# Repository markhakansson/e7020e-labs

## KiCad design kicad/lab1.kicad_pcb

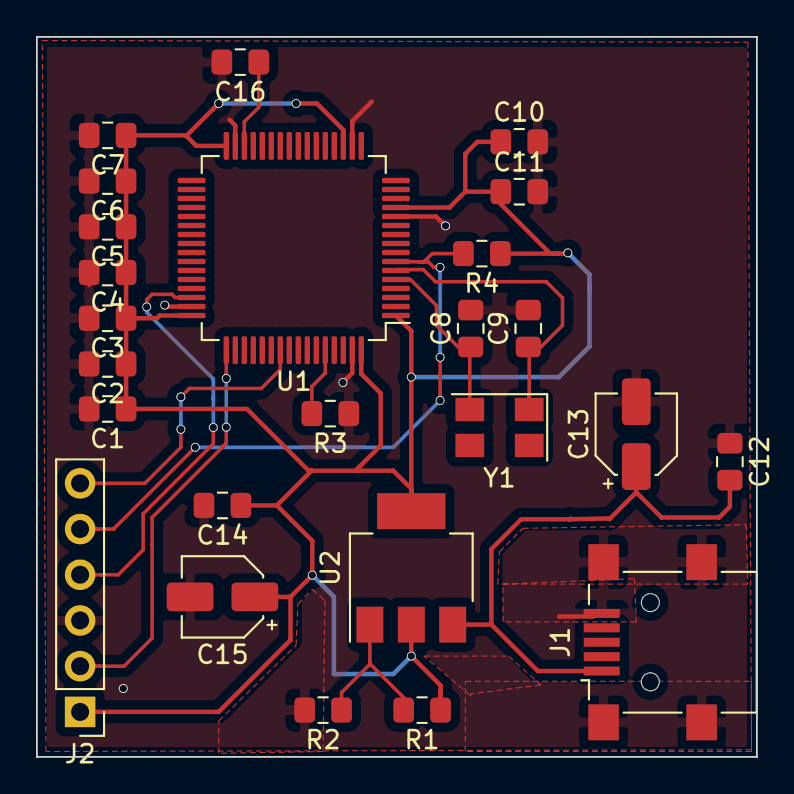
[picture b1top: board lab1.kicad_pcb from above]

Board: 2 copper layers, 40.0 x 40.0 mm, 25 parts (0 on the bottom side), 12 nets.

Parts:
C1, C2, C3, C4, C5, C6, C10, C12, C14: 100nF; C_0805_2012Metric_Pad1.15x1.40mm_HandSolder
C7, C16: 4.7uF; C_0805_2012Metric_Pad1.15x1.40mm_HandSolder
C8, C9: 18pF; C_0805_2012Metric_Pad1.15x1.40mm_HandSolder
C11: 1uF; C_0805_2012Metric_Pad1.15x1.40mm_HandSolder
C13, C15: 10uF; CP_Elec_4x4.5
J1: USB_OTG; USB_Mini-B_Lumberg_2486_01_Horizontal
J2: Conn_01x06_Male; PinHeader_1x06_P2.54mm_Vertical
R1: 2k; R_0805_2012Metric_Pad1.15x1.40mm_HandSolder
R2: 1k; R_0805_2012Metric_Pad1.15x1.40mm_HandSolder
R3, R4: 10k; R_0805_2012Metric_Pad1.15x1.40mm_HandSolder
U1: STM32F411RETx; LQFP-64_10x10mm_P0.5mm
U2: LM1117ADJ; SOT-223
Y1: 8.0Mhz; Crystal_SMD_5032-4Pin_5.0x3.2mm

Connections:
+3V3: C1.1, C2.1, C3.1, C4.1, C5.1, C6.1, C7.1, C10.1, C11.1, C14.1, C15.1, J2.1, R1.1, R4.1, U1.1, U1.13, U1.19, U1.32, U1.48, U1.64, U2.2, U2.4
+5V: C12.2, C13.1, J1.1, U2.3
/NRST: J2.5, R4.2, U1.7
/SWCLK: J2.2, U1.49
/SWDIO: J2.4, U1.46
/SWO: J2.6, U1.55
GND: C1.2, C2.2, C3.2, C4.2, C5.2, C6.2, C7.2, C8.2, C9.2, C10.2, C11.2, C12.1, C13.2, C14.2, C15.2, C16.2, J1.5, J1.6, J2.3, R2.2, R3.1, U1.12, U1.18, U1.31, U1.47, U1.63
unnamed: C8.1, U1.5, Y1.2
unnamed: C9.1, U1.6, Y1.1
unnamed: C16.1, U1.30
unnamed: R1.2, R2.1, U2.1
unnamed: R3.2, U1.60

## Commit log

2020-01-22 Lab 1 1.1 to 1.7 complete
2020-01-23 Finish 1.8-1.10
2020-01-23 Add footprint to most components
2020-01-24 Finish lab 1
2020-01-27 Finish lab 1 for real
2020-01-28 Start work on lab2
2020-01-29 Start routing copper in lab 2
2020-01-30 Finish routing, start work on adding GND plate
2020-02-03 Finish lab 2
2020-04-08 Add Rust bare labs
2020-04-08 Change name from lab1 to kicad
2020-04-08 (bare1_1) answer
2020-04-08 (bare1_2) answer
2020-04-08 (bare1_3) answer
2020-04-08 (bare1_4) answer
2020-04-10 (bare 2_1) finish bare 2
2020-04-11 (bare3_1) answers to question 1
2020-04-11 (bare3_2) add explicit types
2020-04-11 (bare3_3) answer question 3
2020-04-11 (bare3_4) push bs content into a
2020-04-11 (bare3_5) push bs content into a without loop
2020-04-11 (bare0_1) answer question 1
2020-04-11 (bare0_2) answer question 1
2020-04-11 (bare0_3) answer question 3
2020-04-11 (bare0_4) answer question 4
2020-04-11 (bare0_5) answer question 5
2020-04-12 (bare5_1) I did not enjoy the blinking
2020-04-12 (bare4_2) I did not enjoy the blinking
2020-04-12 Remove ./lab1 kicad files, as they are placed in ./kicad
2020-04-12 (bare4_3) answer question 3
2020-04-12 Update toml
2020-04-13 (bare5_1) answer 5.1
2020-04-13 (bare5_2) finish bare 5
